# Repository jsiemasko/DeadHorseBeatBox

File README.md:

# DeadHorse BeatBox

##DO NOT USE. Not yet suitable for humans.  

DeadHorse BeatBox if a drum machine based off of the [Teensy 3.6](https://www.pjrc.com/store/teensy36.html) and two [Adafruit Trellis](https://learn.adafruit.com/adafruit-trellis-diy-open-source-led-keypad/overview).

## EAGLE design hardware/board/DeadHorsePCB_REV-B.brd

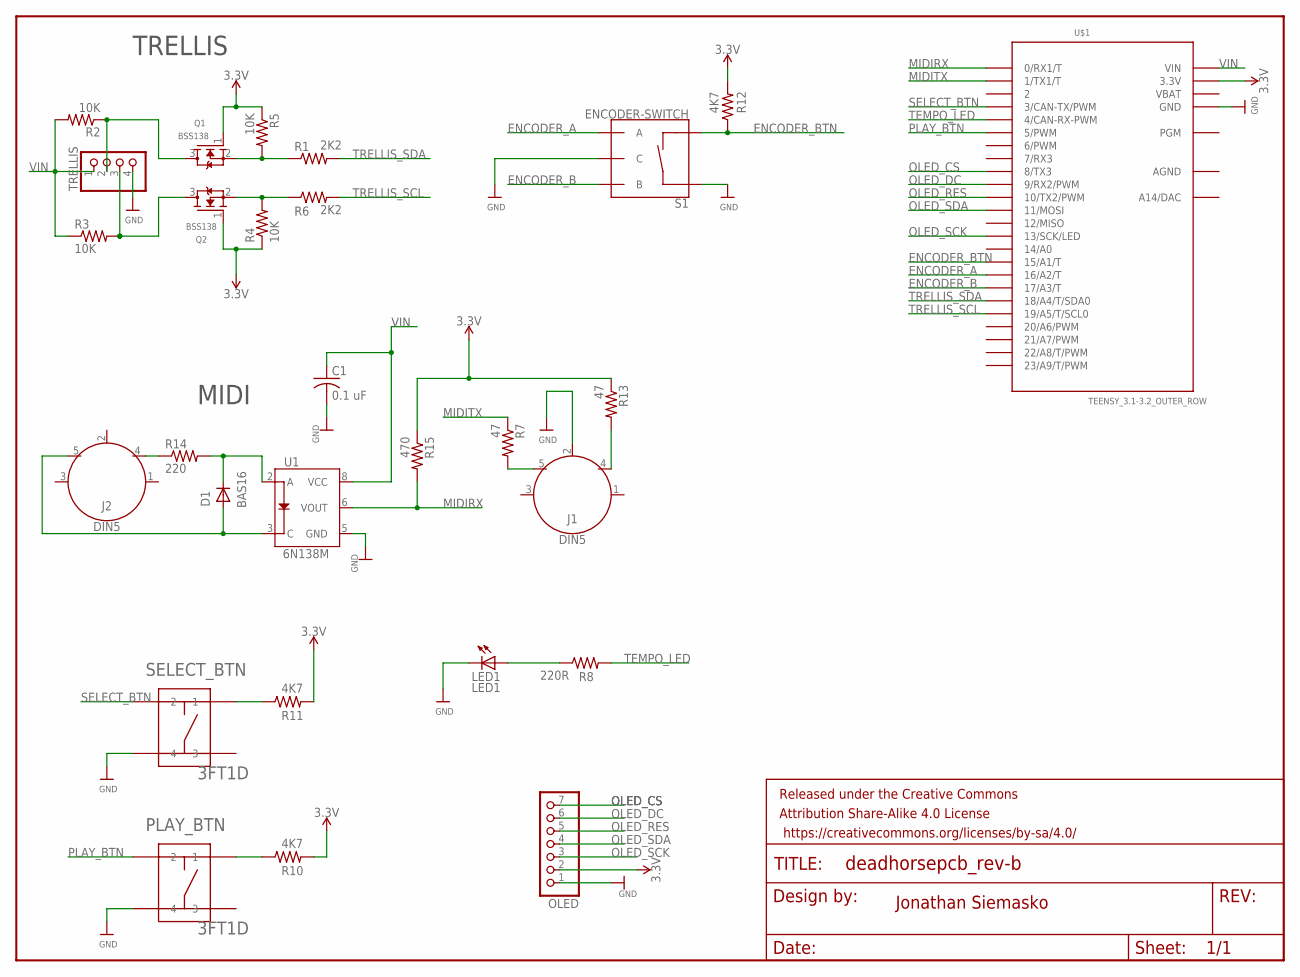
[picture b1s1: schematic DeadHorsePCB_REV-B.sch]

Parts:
C1: 0.1 uF; C0805
D1: BAS16; SOT23
FRAME1: FRAME-LETTER; CREATIVE_COMMONS
J1, J2: DIN5; DIN5-RA-PTH
LED1: LED1; LED5MM
OLED: OLED; 1X07
PLAY_BTN: 3FT1D; 3FT
Q1, Q2: BSS138; SOT23
R1, R6: 2K2; R0805
R2, R3, R4, R5: 10K; R0805
R7, R13: 47; R0805
R8: 220R; R0805
R10, R11, R12: 4K7; R0805
R14: 220; R0805
R15: 470; R0805
S1: ENCODER-SWITCH; ROTARY_ENC_PLAIN
SELECT_BTN: 3FT1D; 3FT
TRELLIS: TRELLIS; 1X04
U1: 6N138M; 8-SMD
U$1: TEENSY_3.1-3.2_OUTER_ROW; TEENSY_3.0-3.2&LC_OUTER_ROW

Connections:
3.3V: OLED.2, Q1.1 (G), Q2.1 (G), R4.1, R5.1, R10.2, R11.2, R12.2, R13.1, R15.1, U$1.3.3V, U$1.3.3V1 (3.3V)
AGND: U$1.AGND
ENCODER_A: S1.A, U$1.16/A2 (16/A2/T)
ENCODER_B: S1.B, U$1.17/A3 (17/A3/T)
ENCODER_BTN: R12.1, S1.SW-, U$1.15/A1 (15/A1/T)
GND: C1.2, J1.2, LED1.K (C), OLED.1, PLAY_BTN.P$4 (4), S1.C, S1.SW+, SELECT_BTN.P$4 (4), TRELLIS.4, U1.5 (GND), U$1.GND, U$1.GND1 (GND)
MIDIRX: R15.2, U1.6 (VOUT), U$1.0 (0/RX1/T)
MIDITX: R7.1, U$1.1 (1/TX1/T)
unnamed: LED1.A, R8.1
unnamed: Q1.3 (D), R2.1, TRELLIS.2
unnamed: J1.4, R13.2
unnamed: J1.5, R7.2
unnamed: Q1.2 (S), R1.1, R5.2
unnamed: J2.4, R14.1
unnamed: D1.3 (K), R14.2, U1.2 (A)
unnamed: Q2.3 (D), R3.2, TRELLIS.3
unnamed: D1.1 (A), J2.5, U1.3 (C)
unnamed: R11.1, SELECT_BTN.P$1 (1)
unnamed: PLAY_BTN.P$1 (1), R10.1
unnamed: Q2.2 (S), R4.2, R6.1
OLED_CS: OLED.7, U$1.8 (8/TX3)
OLED_DC: OLED.6, U$1.9 (9/RX2/PWM)
OLED_RES: OLED.5, U$1.10 (10/TX2/PWM)
OLED_SCK: OLED.3, U$1.13 (13/SCK/LED)
OLED_SDA: OLED.4, U$1.11 (11/MOSI)
PLAY_BTN: PLAY_BTN.P$2 (2), U$1.5 (5/PWM)
SELECT_BTN: SELECT_BTN.P$2 (2), U$1.3 (3/CAN-TX/PWM)
TEMPO_LED: R8.2, U$1.4 (4/CAN-RX-PWM)
TRELLIS_SCL: R6.2, U$1.19/A5 (19/A5/T/SCL0)
TRELLIS_SDA: R1.2, U$1.18/A4 (18/A4/T/SDA0)
VBAT: U$1.VBAT
VIN: C1.1, R2.2, R3.1, TRELLIS.1, U1.8 (VCC), U$1.VIN

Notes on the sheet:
Jonathan Siemasko
TRELLIS
MIDI

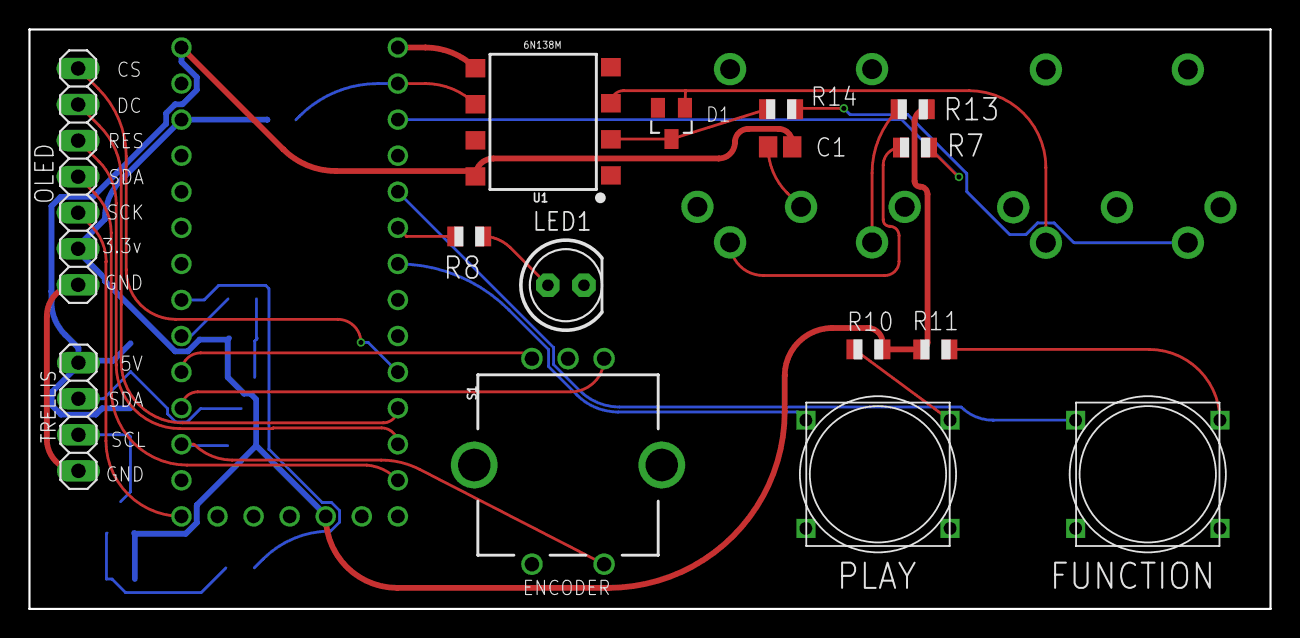
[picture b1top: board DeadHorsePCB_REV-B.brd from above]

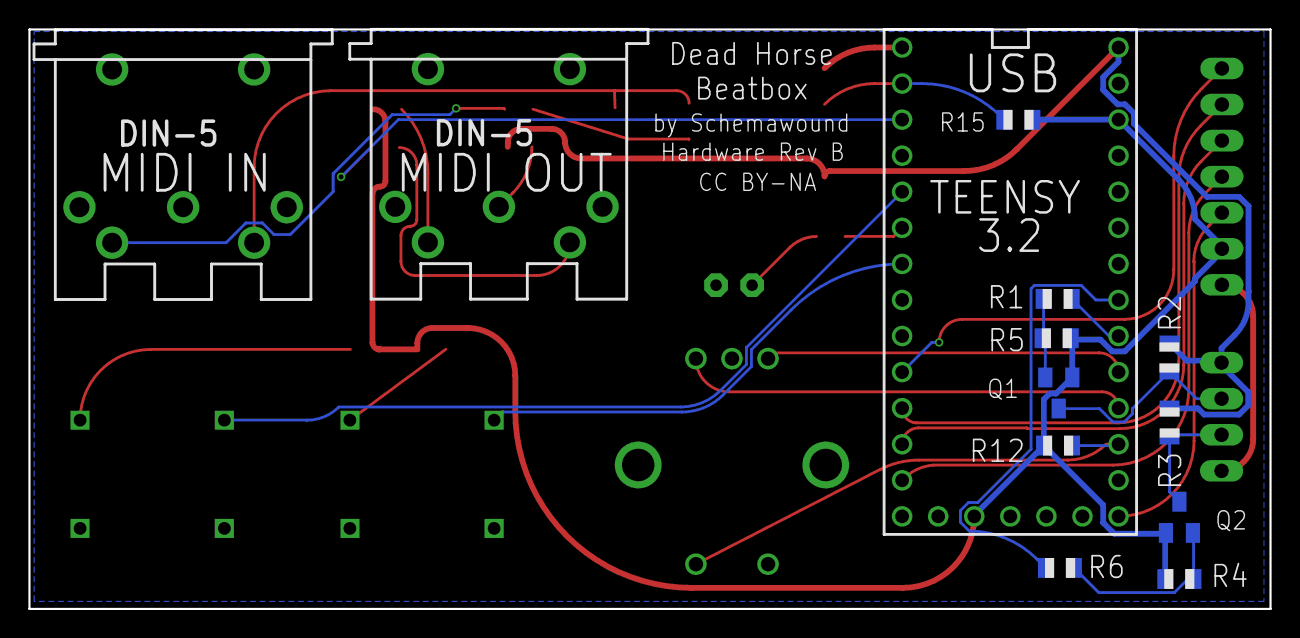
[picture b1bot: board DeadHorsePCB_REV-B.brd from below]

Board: 2 copper layers, 87.4 x 40.8 mm, 29 parts (13 on the bottom side), 30 nets.

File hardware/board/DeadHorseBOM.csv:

Qty,Value,Device,Package,Parts,Description,MF,MPN,OC_FARNELL,OC_NEWARK,PROD_ID
4,10K,R-US_R0805,R0805,"R2, R3, R4, R5","RESISTOR, American symbol",,,,,
2,220R,R-US_R0805,R0805,"R8, R10","RESISTOR, American symbol",,,,,
2,2K2,R-US_R0805,R0805,"R1, R6","RESISTOR, American symbol",,,,,
2,47,R-US_R0805,R0805,"R7, R13","RESISTOR, American symbol",,,,,
3,4K7,R-US_R0805,R0805,"R9, R11, R12","RESISTOR, American symbol",,,,,
2,BSS138,MOSFET-NREFLOW,SOT23,"Q1, Q2",N-Channel Mosfet,,,,,
1,DIN5,DIN5,DIN5-RA-PTH,J1,DIN5 Connector - Female Right Angle (frequently used as a MIDI Jack connector),,,,,CONN-09481
1,ENCODER,MA05-1,MA05-1,ENCODER,PIN HEADER,,,unknown,unknown,
1,OLED,PINHD-1X7,1X07,OLED,PIN HEADER,,,,,
1,PlayBtn,PINHD-1X4,1X04,PLAY_BUTTON,PIN HEADER,,,,,
1,SelectBtn,PINHD-1X4,1X04,SELECT_BUTTON,PIN HEADER,,,,,
1,TEENSY_3.6_DIL,TEENSY_3.6_DIL,TEENSY_3.6_DIL,U$8,Teensy 3.6 DIL Package,,,,,
1,TRELLIS,PINHD-1X4,1X04,TRELLIS,PIN HEADER,,,,,

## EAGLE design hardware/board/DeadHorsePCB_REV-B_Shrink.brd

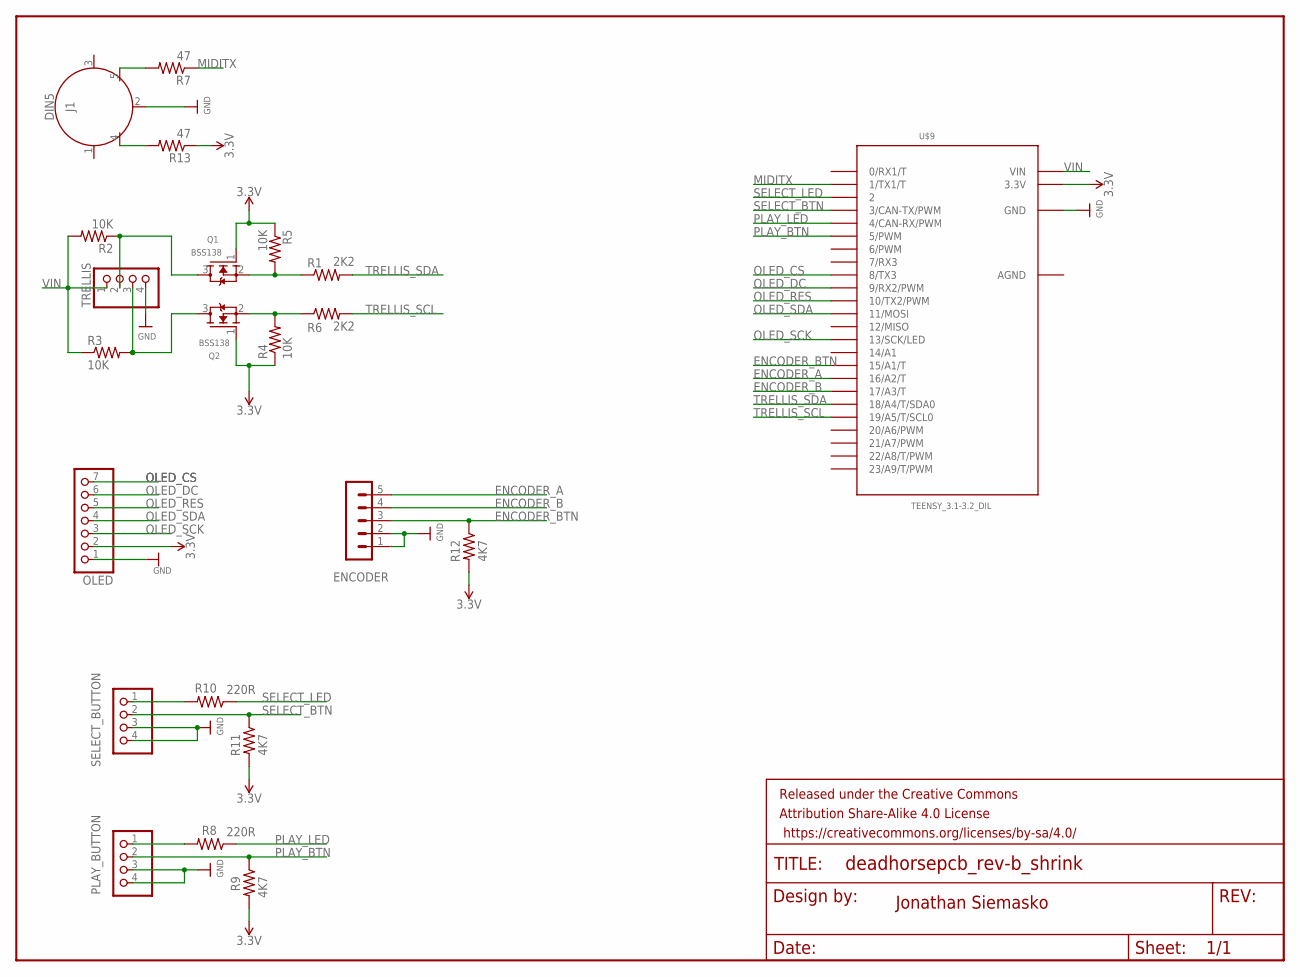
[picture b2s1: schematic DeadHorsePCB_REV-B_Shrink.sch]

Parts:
ENCODER: ENCODER; MA05-1
FRAME1: FRAME-LETTER; CREATIVE_COMMONS
J1: DIN5; DIN5-RA-PTH
OLED: OLED; 1X07
PLAY_BUTTON: PlayBtn; 1X04
Q1, Q2: BSS138; SOT23
R1, R6: 2K2; R0805
R2, R3, R4, R5: 10K; R0805
R7, R13: 47; R0805
R8, R10: 220R; R0805
R9, R11, R12: 4K7; R0805
SELECT_BUTTON: SelectBtn; 1X04
TRELLIS: TRELLIS; 1X04
U$9: TEENSY_3.1-3.2_DIL; TEENSY_3.0-3.2&LC_DIL

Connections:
3.3V: OLED.2, Q1.1 (G), Q2.1 (G), R4.1, R5.1, R9.2, R11.2, R12.2, R13.1, U$9.3.3V
AGND: U$9.AGND
ENCODER_A: ENCODER.5, U$9.16/A2 (16/A2/T)
ENCODER_B: ENCODER.4, U$9.17/A3 (17/A3/T)
ENCODER_BTN: ENCODER.3, R12.1, U$9.15/A1 (15/A1/T)
GND: ENCODER.1, ENCODER.2, J1.2, OLED.1, PLAY_BUTTON.3, PLAY_BUTTON.4, SELECT_BUTTON.3, SELECT_BUTTON.4, TRELLIS.4, U$9.GND
MIDITX: R7.1, U$9.1 (1/TX1/T)
unnamed: PLAY_BUTTON.1, R8.2
unnamed: Q1.3 (D), R2.1, TRELLIS.2
unnamed: J1.4, R13.2
unnamed: J1.5, R7.2
unnamed: Q1.2 (S), R1.1, R5.2
unnamed: Q2.3 (D), R3.2, TRELLIS.3
unnamed: Q2.2 (S), R4.2, R6.1
unnamed: R10.2, SELECT_BUTTON.1
OLED_CS: OLED.7, U$9.8 (8/TX3)
OLED_DC: OLED.6, U$9.9 (9/RX2/PWM)
OLED_RES: OLED.5, U$9.10 (10/TX2/PWM)
OLED_SCK: OLED.3, U$9.13 (13/SCK/LED)
OLED_SDA: OLED.4, U$9.11 (11/MOSI)
PLAY_BTN: PLAY_BUTTON.2, R9.1, U$9.5 (5/PWM)
PLAY_LED: R8.1, U$9.4 (4/CAN-RX/PWM)
SELECT_BTN: R11.1, SELECT_BUTTON.2, U$9.3 (3/CAN-TX/PWM)
SELECT_LED: R10.1, U$9.2
TRELLIS_SCL: R6.2, U$9.19/A5 (19/A5/T/SCL0)
TRELLIS_SDA: R1.2, U$9.18/A4 (18/A4/T/SDA0)
VIN: R2.2, R3.1, TRELLIS.1, U$9.VIN

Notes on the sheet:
Jonathan Siemasko

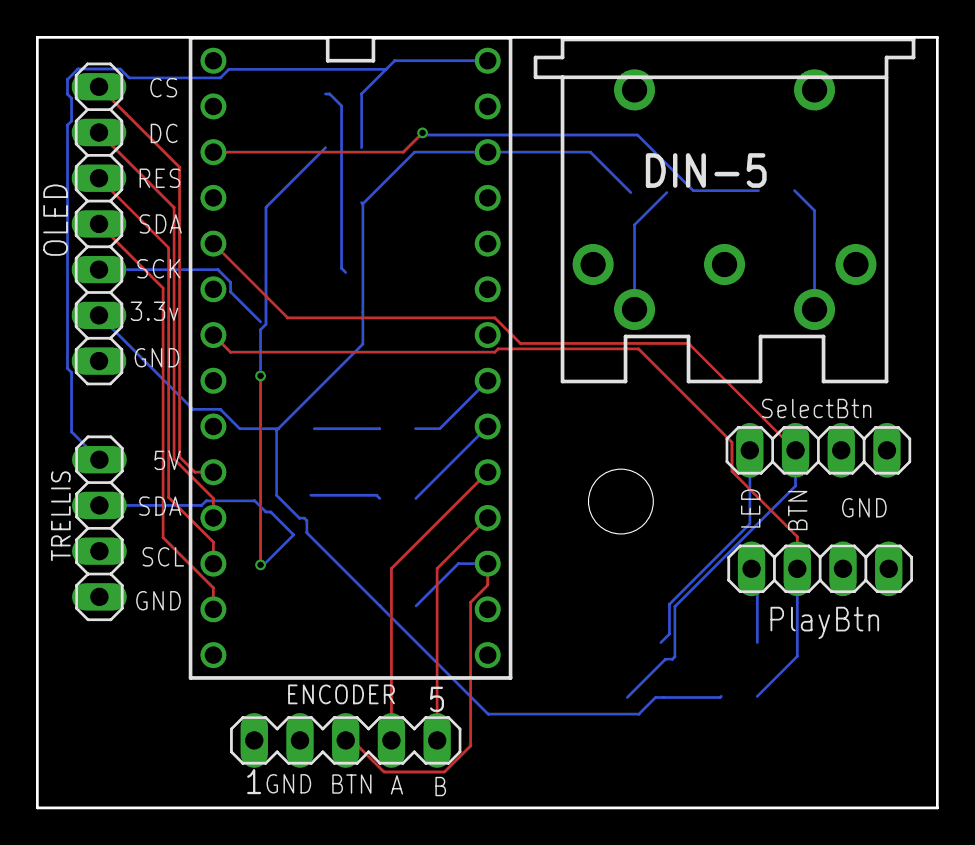
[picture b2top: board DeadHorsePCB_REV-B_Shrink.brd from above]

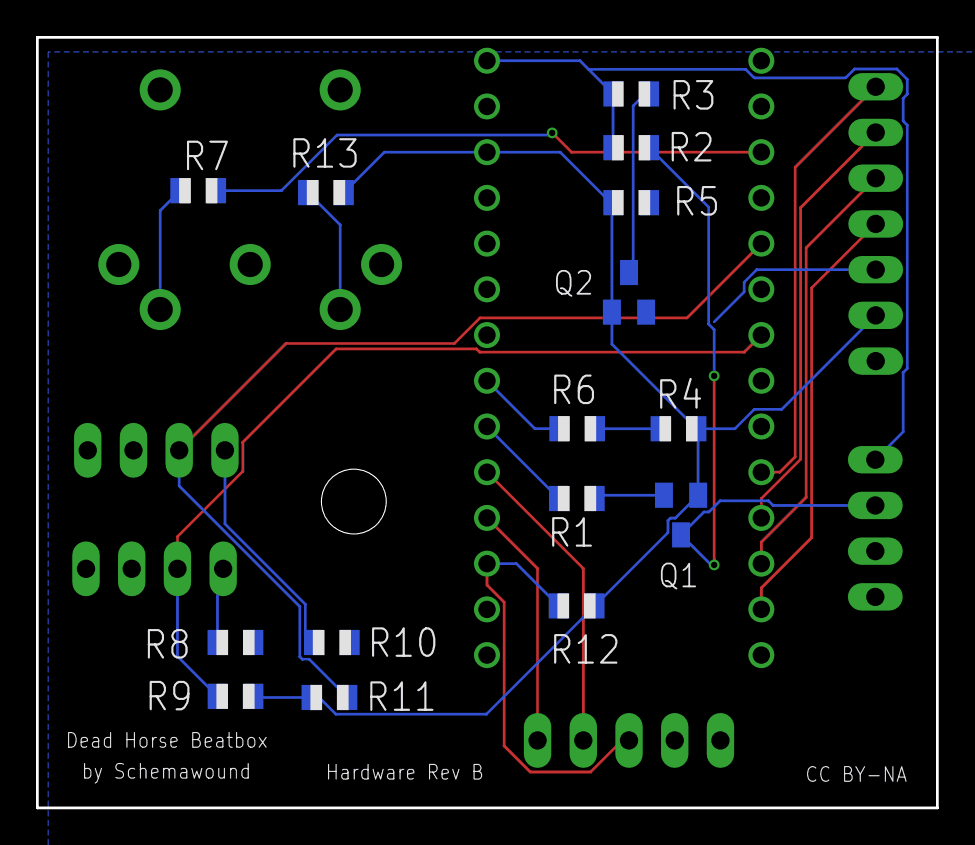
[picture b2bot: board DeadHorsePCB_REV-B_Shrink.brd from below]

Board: 2 copper layers, 50.0 x 42.8 mm, 23 parts (15 on the bottom side), 26 nets.

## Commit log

2017-12-04 Initial creation of project
2017-12-04 Added _vm to ignore
2017-12-05 Removed release folder from project
2017-12-05 Removed debug from project
2017-12-05 Removed mystery nested duplicate from project. Learning Git. Hooray.
2017-12-05 Splitting software and hardware
2017-12-05 Housekeeping
2017-12-05 Added first panel that was printed
2017-12-05 Deleted old laser print template
2017-12-05 Added LICENSE.md
2017-12-06 Moved to folder with project name per Arduino requirement
2017-12-06 Edited README.md
2017-12-06 Fixed tempo adjust bug Set tempo limits Tried to improve latency
2017-12-07 Fixed Encoder Button Cleaned up display code
2017-12-11 Fixed cursor flash bug in quad mode Implemented burst mode
2017-12-11 Updated Mode Cheatsheet.xlsx
2017-12-13 Working out final mode list
2017-12-19 Updated documentation to work towards 16 step mode
2017-12-20 Moved tempo LED to play button
2017-12-20 First draft of 16 step change
2017-12-22 Fixed flashing
2017-12-31 Moved from 4 modes per light to two
2017-12-31 Display changes
2018-01-03 Added track and step display
2018-01-04 bargraph
2018-01-04 Display Tweaks
2018-01-05 Graphics Tweaks
2018-01-05 Step Display
2018-01-05 Moar display tweaks!
2018-01-07 Changing step object, Serial output
2018-01-08 Removed workload on track, brought step back
2018-01-09 Improved track display, removed uneeded redirection in pattern, fixed all modes, fixed encoder response
2018-01-09 Added Step Jump
2018-01-09 Fixed retrigger code
2018-01-10 Velocity Sensitive Bargraph
2018-01-11 Start/stop implemented. Seperated animations from playing clock.
2018-01-17 Midway commit before pulling Trellis specific code from the Grid class
2018-01-17 DHTrellis display fixed
2018-01-18 Fixed button entry
2018-01-22 Added DIN MIDI
2018-01-23 Added board files
2018-01-23 Further board modifications
2018-01-23 Getting closer on the PCB
2018-01-24 Added Ground Plane
2018-01-24 Ripup
2018-01-25 Submitted PCB Rev A for manufacturing. Started BOM
2018-01-28 Breaking into namespaces
2018-01-29 Reorg of namespaces
2018-01-31 Added revised step display
2018-02-01 Seperated display to view and controller
2018-02-03 Moved LEDs to display namespace
2018-02-10 Redesigning...
2018-02-11 Hardware Rev B

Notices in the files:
hardware/board/DeadHorsePCB_REV-B.brd:
CC BY-NA
parts and their libraries:
SparkFun-Aesthetics: Licensing: Creative Commons ShareAlike 4.0 International - https://creativecommons.org/licenses/by-sa/4.0
SparkFun-Aesthetics: Released under the Creative Commons Attribution Share-Alike 4.0 License
SparkFun-Aesthetics: https://creativecommons.org/licenses/by-sa/4.0
